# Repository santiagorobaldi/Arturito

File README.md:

# Arturito

Arturito es un proyecto desarrollado para la materia "Taller de Proyecto I" de la Facultad de Ingeniería de la Universidad Nacional de La Plata (UNLP).  

El proyecto propone un rover de tracción diferencial que combine mediciones de distancia, información inercial y giro de las ruedas para estimar su posición y construir un mapa de ocupación 2D del entorno el cual pueda visualizarse en un dispositivo externo, asi como tambien que sea capaz de navegar el entorno de manera autonoma para la generacion completa del mapa. 

## Organización del repositorio

| Carpeta | Contenido |
| --- | --- |
| `firmware/shared/layer1_hal/` | Contratos de capa HAL. |
| `firmware/shared/layer2_drivers/` | Drivers para la utilización de sensores y modulos integrados. |
| `firmware/shared/layer3_app/` | Lógica compartida de la aplicación y coordinación de las tareas de lectura, procesamiento y envío de datos con FreeRTOS (Runtime). |
| `firmware/EDU-CIAA/` | Configuración de compilación, bibliotecas, inicialización de la aplicación y acceso al hardware de EDU-CIAA. |
| `firmware/ESP32/` | Proyecto PlatformIO con Arduino, inicialización de la aplicación y acceso al hardware de ESP32. |
| `docs/` | Documentación técnica y decisiones. |
| `KiCad/` | Esquemáticos y diseño de PCB. |
| `utils/` | Herramientas de PC |
| `utils/Processing/` | Visualización de orientación y lecturas de distancia. |

Arturito.code-workspace define las carpetas que VS Code abre como raíces del área de trabajo. Cada raíz puede tener su propia configuración del editor y ser reconocida por las extensiones. Por ejemplo, incluir firmware/ESP32 como raíz permite que PlatformIO encuentre su archivo platformio.ini y muestre las herramientas para compilar y cargar el firmware en la placa. Estas referencias no mueven ni duplican las carpetas del proyecto.

## Documentación

Este README ofrece una vista general del proyecto y sirve como punto de entrada a la documentación. Cada documento desarrolla un aspecto específico:

- [Descripción del sistema](docs/system-overview.md): explica cómo está compuesto el robot mediante el diagrama de bloques funcionales y describe la función de cada bloque y sus relaciones.
- [Arquitectura del firmware](docs/software-architecture.md): detalla las capas, sus interfaces y cómo se distribuyen en las carpetas del repositorio. 
- [Hardware](docs/hardware.md): reúne los componentes y sus características relevantes, su distribución en los bloques del sistema y sus conexiones. Sirve de guía para consultar los esquemáticos del proyecto en `KiCad/`.
- [Requisitos](docs/requirements.md): detalla qué debe cumplir el proyecto y cómo verificar cada requisito, vinculándolo con criterios de aceptación y pruebas de validación.
- [Preparación, compilación y ejecución](docs/build-and-run.md): indica qué herramientas se necesitan, cómo configurar el entorno, compilar y cargar el firmware en las placas, y poner en marcha la visualización y los programas de prueba.
- [Decisiones de diseño — ADR](docs/decisions/README.md): registra las decisiones importantes del proyecto, su contexto, justificación y consecuencias. Los demás documentos remiten aquí para explicar las elecciones de diseño.
- [Registro de desarrollo](docs/development-status.md): guarda el estado actual de los diferentes modulos o bloques a desarrollar para llevar un registro de lo realizado, lo validado, y lo que queda pendiente de desarrollo.

## Cómo empezar

Leé primero la [descripción del sistema](docs/system-overview.md) y luego la [arquitectura de software](docs/software-architecture.md). Para preparar las herramientas, compilar y ejecutar los programas de prueba, seguí [build-and-run.md](docs/build-and-run.md).

## Autores

Joaquín Guzmán, Tomás Gamarra, Santiago Robaldi y Federico Goncalves.

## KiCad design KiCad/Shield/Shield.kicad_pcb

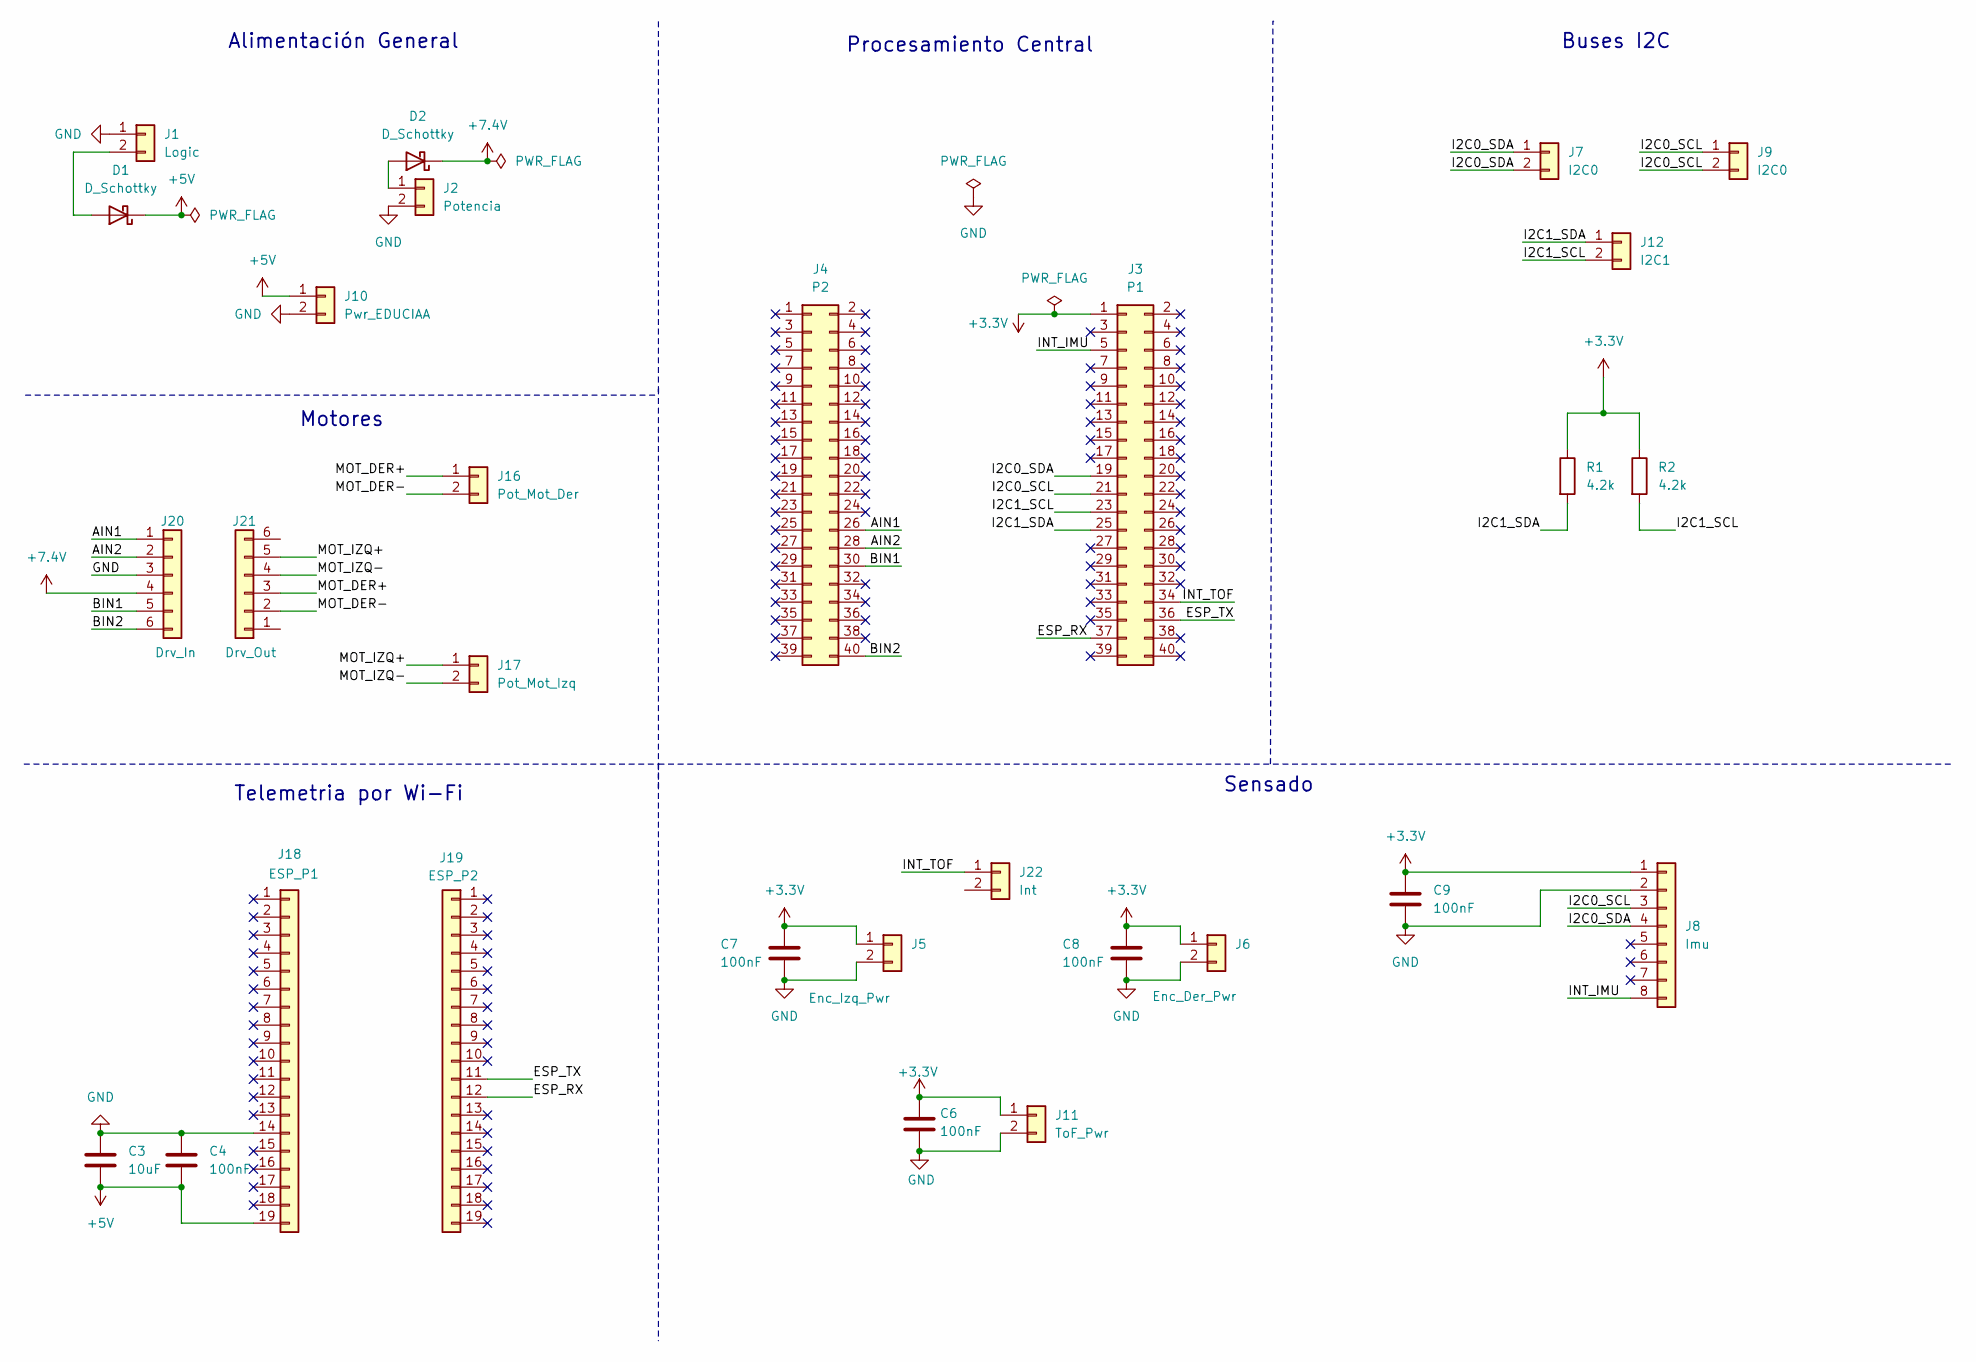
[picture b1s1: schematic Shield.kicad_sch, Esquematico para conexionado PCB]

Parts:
C3: 10uF; CP_Radial_D10.0mm_P5.00mm
C4, C6, C7, C8, C9: 100nF; C_Disc_D3.0mm_W1.6mm_P2.50mm
D1, D2: D_Schottky; D_A-405_P7.62mm_Horizontal
J1: Logic; TerminalBlock_Phoenix_MPT-0,5-2-2.54_1x02_P2.54mm_Horizontal
J2: Potencia; TerminalBlock_Phoenix_MPT-0,5-2-2.54_1x02_P2.54mm_Horizontal
J3: P1; PinHeader_2x20_P2.54mm_Vertical
J4: P2; PinHeader_2x20_P2.54mm_Vertical
J5: Enc_Izq_Pwr; TerminalBlock_Phoenix_MPT-0,5-2-2.54_1x02_P2.54mm_Horizontal
J6: Enc_Der_Pwr; TerminalBlock_Phoenix_MPT-0,5-2-2.54_1x02_P2.54mm_Horizontal
J7, J9: I2C0; TerminalBlock_Phoenix_MPT-0,5-2-2.54_1x02_P2.54mm_Horizontal
J8: Imu; PinSocket_1x08_P2.54mm_Vertical
J10: Pwr_EDUCIAA; TerminalBlock_Phoenix_MPT-0,5-2-2.54_1x02_P2.54mm_Horizontal
J11: ToF_Pwr; TerminalBlock_Phoenix_MPT-0,5-2-2.54_1x02_P2.54mm_Horizontal
J12: I2C1; TerminalBlock_Phoenix_MPT-0,5-2-2.54_1x02_P2.54mm_Horizontal
J16: Pot_Mot_Der; TerminalBlock_Phoenix_MPT-0,5-2-2.54_1x02_P2.54mm_Horizontal
J17: Pot_Mot_Izq; TerminalBlock_Phoenix_MPT-0,5-2-2.54_1x02_P2.54mm_Horizontal
J18: ESP_P1; PinSocket_1x19_P2.54mm_Vertical
J19: ESP_P2; PinSocket_1x19_P2.54mm_Vertical
J20: Drv_In; PinSocket_1x06_P2.54mm_Vertical
J21: Drv_Out; PinSocket_1x06_P2.54mm_Vertical
J22: Int; TerminalBlock_Phoenix_MPT-0,5-2-2.54_1x02_P2.54mm_Horizontal
R1, R2: 4.2k; R_Axial_DIN0204_L3.6mm_D1.6mm_P5.08mm_Horizontal

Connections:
+3.3V: C6.1, C7.1, C8.1, C9.1, J3.1, J5.1, J6.1, J8.1, J11.1, R1.1, R2.1
+5V: C3.2, C4.2, D1.1 (K), J10.1, J18.19
+7.4V: D2.1 (K), J20.4
/AIN1: J4.26, J20.1
/AIN2: J4.28, J20.2
/BIN1: J4.30, J20.5
/BIN2: J4.40, J20.6
/ESP_RX: J3.37, J19.12
/ESP_TX: J3.36, J19.11
/I2C0_SCL: J3.21, J8.3, J9.1, J9.2
/I2C0_SDA: J3.19, J7.1, J7.2, J8.4
/I2C1_SCL: J3.23, J12.2, R2.2
/I2C1_SDA: J3.25, J12.1, R1.2
/INT_IMU: J3.5, J8.8
/INT_TOF: J3.34, J22.1 (Pin_1_1)
/MOT_DER+: J16.1, J21.3
/MOT_DER-: J16.2, J21.2
/MOT_IZQ+: J17.1, J21.5
/MOT_IZQ-: J17.2, J21.4
GND: C3.1, C4.1, C6.2, C7.2, C8.2, C9.2, J1.1, J2.2, J5.2, J6.2, J8.2, J10.2, J11.2, J18.14, J20.3
unnamed: D1.2 (A), J1.2
unnamed: D2.2 (A), J2.1

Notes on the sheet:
Procesamiento Central
Sensado
Motores
Buses I2C
Alimentación General
Telemetria por Wi-Fi

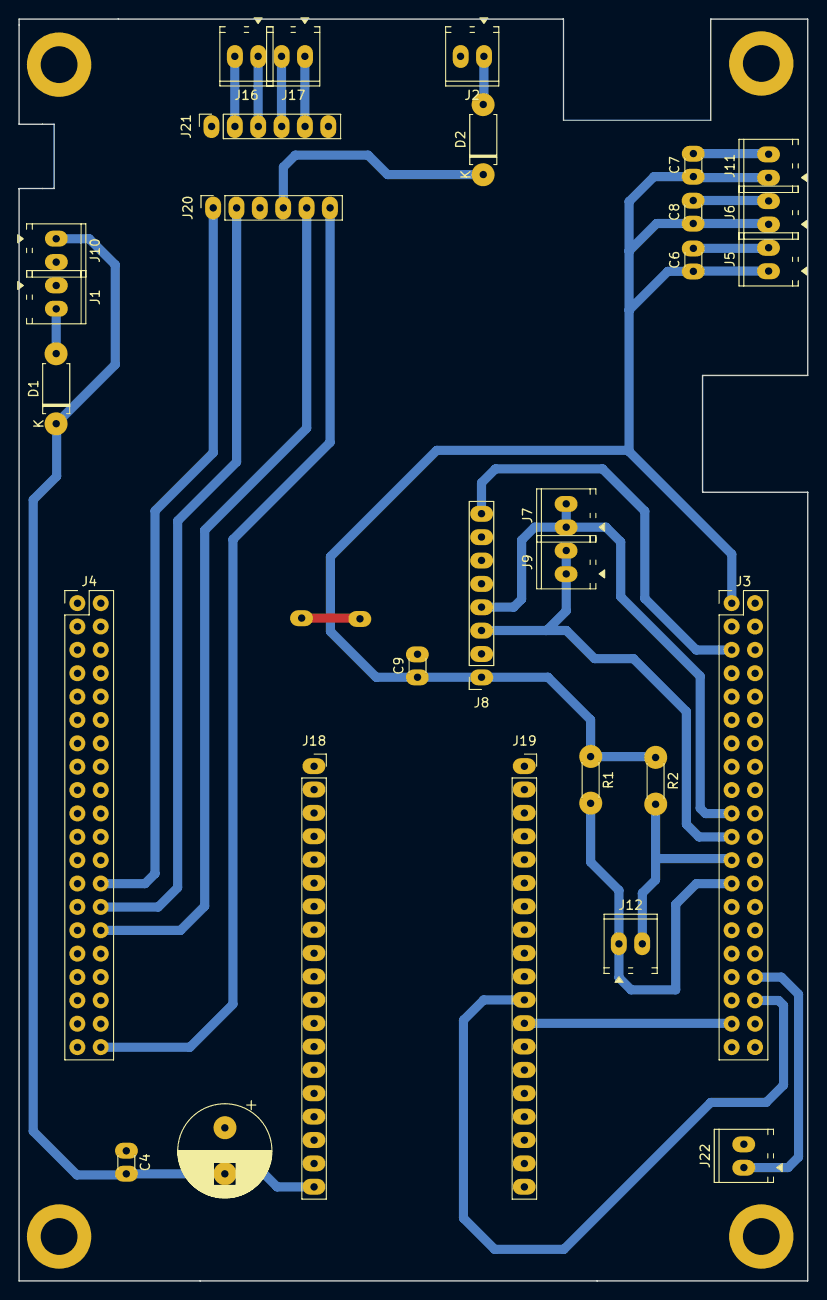
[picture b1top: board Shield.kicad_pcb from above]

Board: 2 copper layers, 85.7 x 137.2 mm, 29 parts (0 on the bottom side), 22 nets.
